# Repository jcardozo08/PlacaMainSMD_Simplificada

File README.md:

# PlacaMainSMD Simplificada

Mesma proposta da [PlacaMainSMD v1](https://github.com/jcardozo08/PlacaMainSMD_v1), mas com uma mistura de componentes **SMD e PTH** e com **módulos fáceis de encontrar** no mercado (GPS NEO-M8N, IMU GY-91, LoRa E32/E22) no lugar dos sensores soldados direto na placa. Assim ela fica mais barata, mais fácil de montar e de consertar em campo, e serve de alternativa robusta à v1.

## Destaques

- **ESP32-S3-WROOM-1**
- Conectores para GPS **u-blox NEO-M8N** e IMU **GY-91 / ICM-20948**
- Rádios LoRa **E22-900T22S** / **E32-915T20D** com conector SMA
- **4 canais de ignição** com MOSFETs SI2300, chave RBF, chave ON/OFF e buzzer
- Bateria de backup **ML414H** e porta USB-A
- **Gerbers** e arquivos de montagem **JLCPCB** incluídos
- Firmware: [FlightCode](https://github.com/jcardozo08/FlightCode) (`PLACA_MAIN_SMD`) / [FlightComputerRTOS](https://github.com/jcardozo08/FlightComputerRTOS)

| Topo | Base |
|:---:|:---:|
|  |  |

## Arquivos

- `PlacaMainSMD_Simplificada.kicad_sch`: esquemático ([ver em SVG](images/schematic.svg))
- `PlacaMainSMD_Simplificada.kicad_pcb`: layout da placa ([ver em SVG](images/layout.svg))
- `jlcpcb/`: Gerbers, furação, BOM e CPL para fabricação
- `PlacaMainSMD_Simplificada.step`: modelo 3D

**Ferramenta:** KiCad

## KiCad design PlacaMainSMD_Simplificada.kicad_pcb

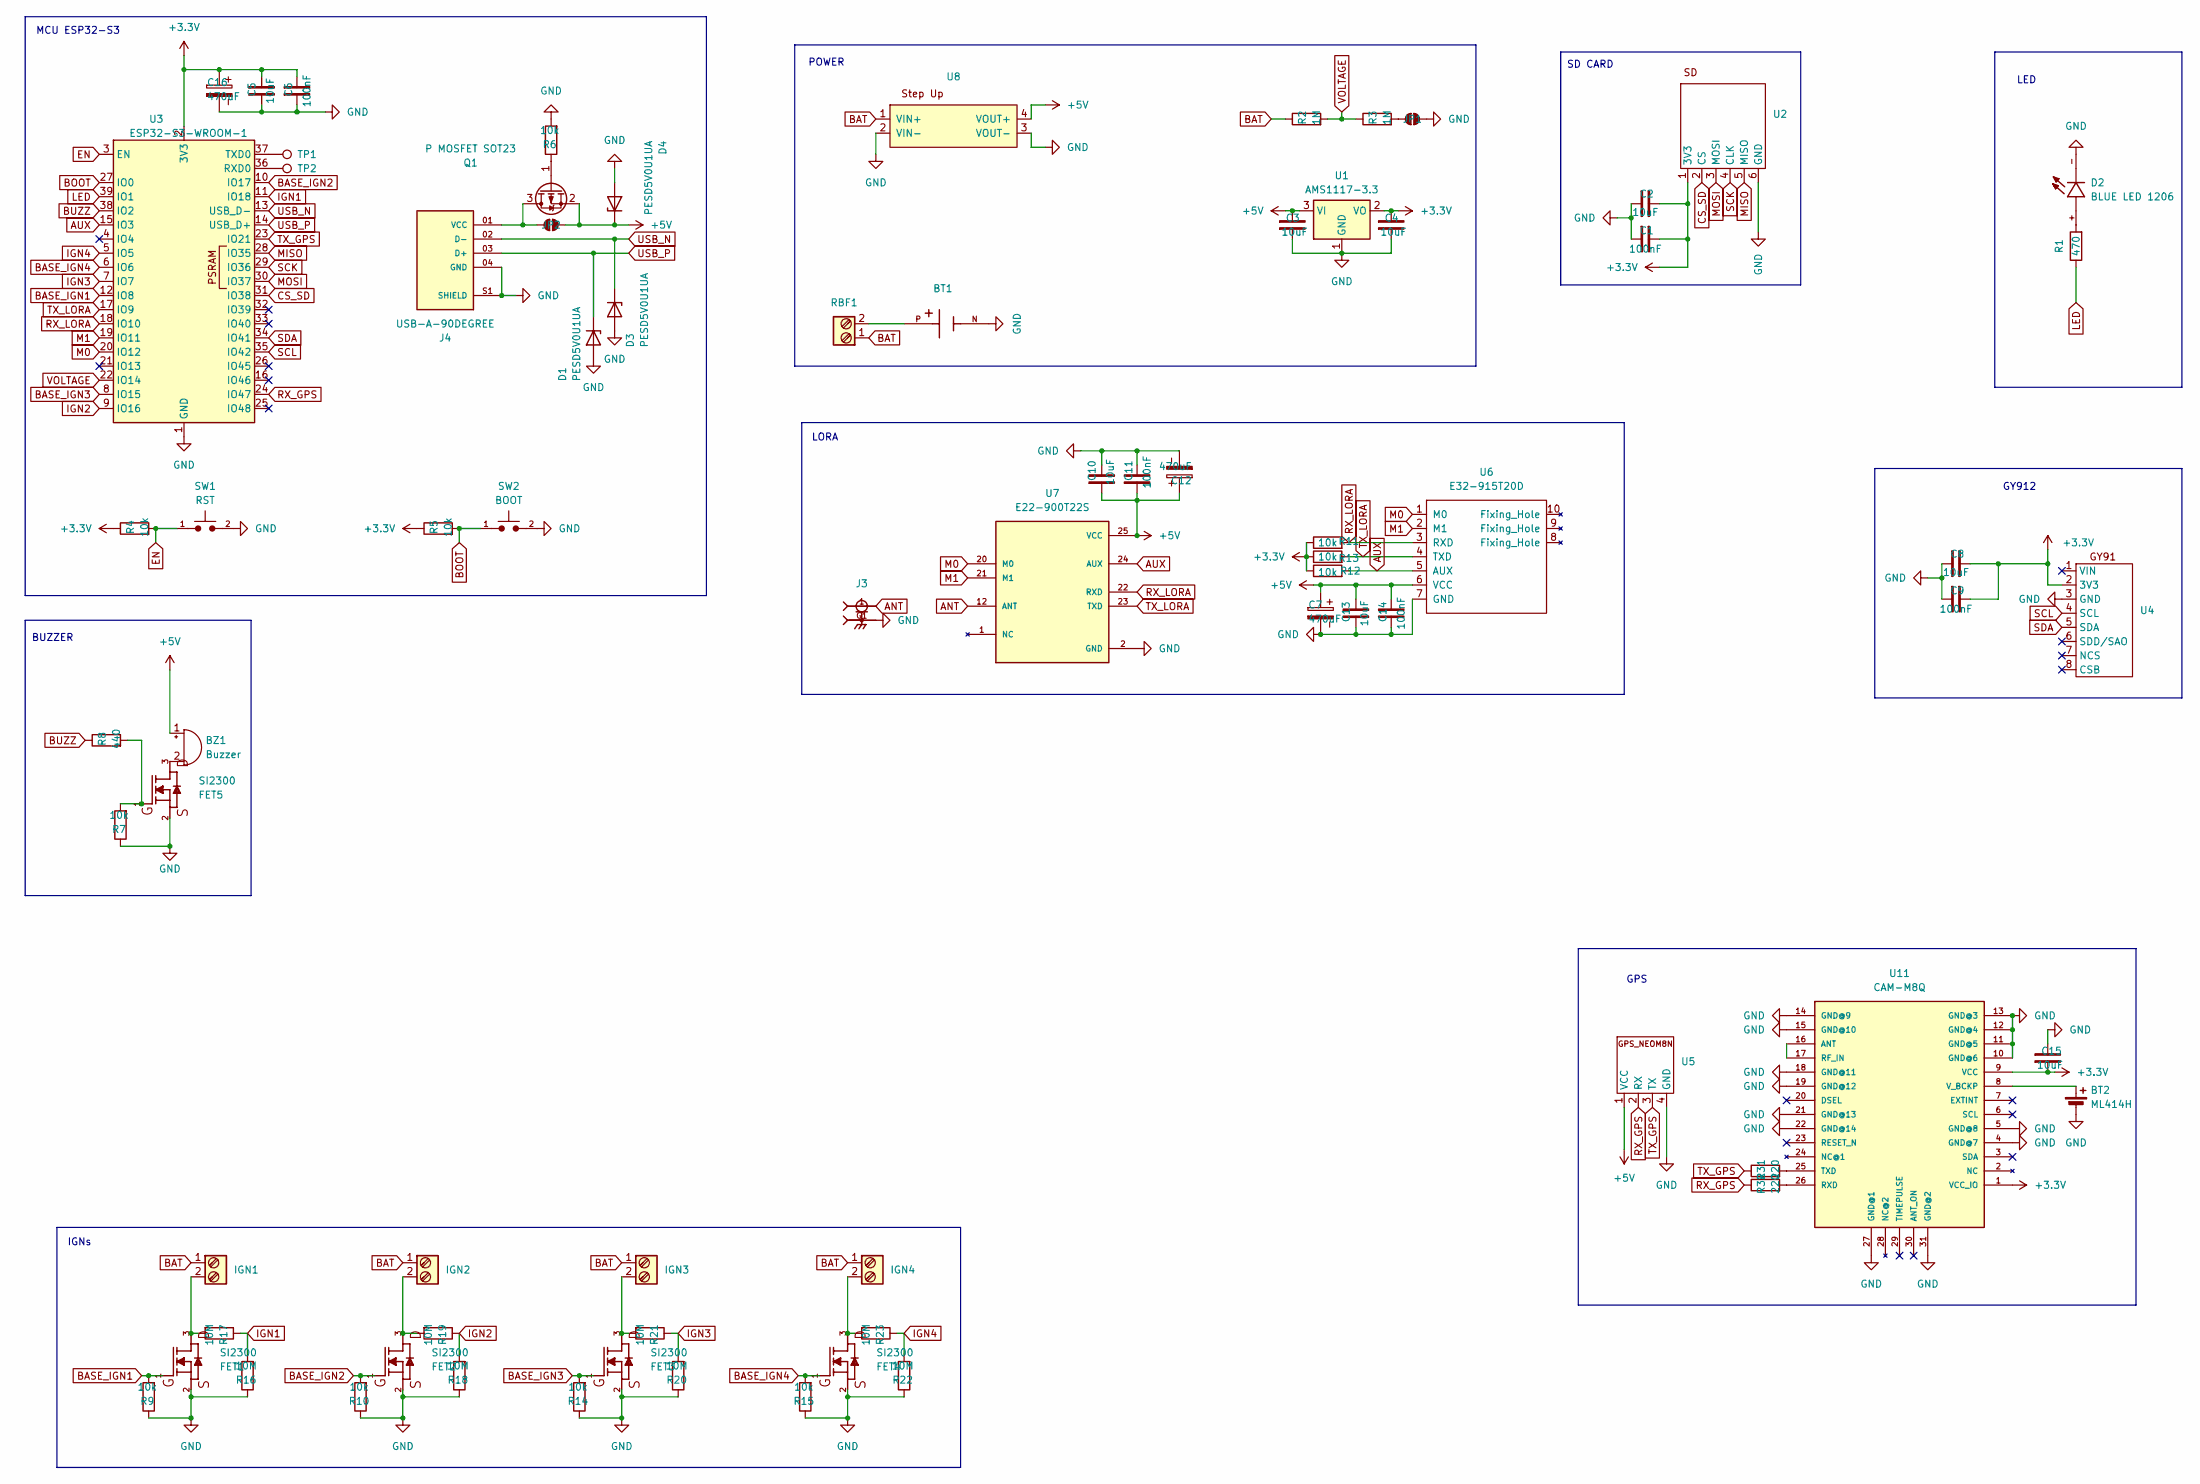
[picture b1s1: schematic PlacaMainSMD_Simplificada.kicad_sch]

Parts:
BT1: 18650_SMD
BT2: ML414H; ML414H_IV01E
BZ1: Buzzer
C1, C6, C9, C11, C14: 100nF; C_0805_2012Metric_Pad1.18x1.45mm_HandSolder
C2, C3, C4, C5, C8, C10, C13, C15: 10uF; C_0805_2012Metric_Pad1.18x1.45mm_HandSolder
C7, C12, C16: 470uF; CP_Radial_D5.0mm_P2.50mm
D1, D3, D4: PESD5V0U1UA; D_SOD-323_HandSoldering
D2: BLUE LED 1206; LED_SMD_1206; PARTREV 2002-04-11
FET1, FET2, FET3, FET4, FET5: SI2300; SOT23_SI2300
IGN1: IGN1; Borne 2 Vias
IGN2: IGN2; Borne 2 Vias
IGN3: IGN3; Borne 2 Vias
IGN4: IGN4; Borne 2 Vias
J3: ConectorSMA_EdgeMount; PARTREV 1
J4: USB-A-90DEGREE; PARTREV R
JP1, JP2: Jumper_2_NO
Q1: P MOSFET SOT23; SOT-23
R1: 470; R_0805_2012Metric_Pad1.20x1.40mm_HandSolder
R2, R3: 1M; R_0805_2012Metric_Pad1.20x1.40mm_HandSolder
R4, R5, R6, R7, R9, R10, R11, R12, R13, R14, R15: 10k; R_0805_2012Metric_Pad1.20x1.40mm_HandSolder
R8: 440; R_0805_2012Metric_Pad1.20x1.40mm_HandSolder
R16, R17, R18, R19, R20, R21, R22, R23: 10M; R_0805_2012Metric_Pad1.20x1.40mm_HandSolder
R31, R32: 220; R_0805_2012Metric_Pad1.20x1.40mm_HandSolder
RBF1: RBF1; Borne 2 Vias
SW1: RST; SW_PUSH_6mm
SW2: BOOT; SW_PUSH_6mm
TP1, TP2: TestPoint
U1: AMS1117-3.3; SOT-223-3_TabPin2
U2: MicroSD_Module_3.3V
U3: ESP32-S3-WROOM-1
U4: GY-91_Module
U5: GPS_NeoM8N
U6: E32-915T20D; E32-xxxT20D
U7: E22-900T22S; PARTREV 1.00
U8: Step Up
U11: CAM-M8Q; CAM-M8

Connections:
+3.3V: C1.2, C2.2, C4.2, C5.2, C6.2, C8.2, C9.2, C15.1, C16.1, R4.1, R5.1, R11.1, R12.1, R13.1, U1.2 (VO), U2.1 (3V3), U3.2 (3V3), U4.2 (3V3), U11.1 (VCC_IO), U11.9 (VCC)
+5V: BZ1.1 (+), C3.2, C7.1, C10.1, C11.1, C12.1, C13.2, C14.2, D4.1 (K), JP2.2 (B), Q1.2 (S), U1.3 (VI), U5.1 (VCC), U6.6 (VCC), U7.25 (VCC), U8.4 (VOUT+)
ANT: J3.1, U7.12 (ANT)
AUX: R13.2, U3.15 (IO3), U6.5 (AUX), U7.24 (AUX)
BASE_IGN1: FET1.1, R9.2, U3.12 (IO8)
BASE_IGN2: FET2.1, R10.2, U3.10 (IO17)
BASE_IGN3: FET3.1, R14.2, U3.8 (IO15)
BASE_IGN4: FET4.1, R15.2, U3.6 (IO6)
BAT: IGN1.1, IGN2.1, IGN3.1, IGN4.1, R2.1, RBF1.1, U8.1 (VIN+)
BOOT: R5.2, SW2.1, U3.27 (IO0)
BUZZ: R8.1, U3.38 (IO2)
CS_SD: U2.2 (CS), U3.31 (IO38)
EN: R4.2, SW1.1, U3.3 (EN)
GND: BT1.N, BT2.-, C1.1, C2.1, C3.1, C4.1, C5.1, C6.1, C7.2, C8.1, C9.1, C10.2, C11.2, C12.2, C13.1, C14.1, C15.2, C16.2, D1.2 (A), D2.-, D3.2 (A), D4.2 (A), FET1.2, FET2.2, FET3.2, FET4.2, FET5.2, J3.G1, J3.G2, J3.G3, J3.G4, J4.04 (GND), J4.S1 (SHIELD), J4.S2 (SHIELD), JP1.2 (B), R6.2, R7.1, R9.1, R10.1, R14.1, R15.1, R16.1, R18.1, R20.1, R22.1, SW1.2, SW2.2, U1.1 (GND), U2.6 (GND), U3.1 (GND), U3.40 (GND), U3.41 (GND), U4.3 (GND), U5.4 (GND), U6.7 (GND), U7.2 (GND), U7.8 (GND), U7.11 (GND), U7.13 (GND), U7.14 (GND), U7.15 (GND), U7.16 (GND), U7.19 (GND), U7.26 (GND), U8.2 (VIN-), U8.3 (VOUT-), U11.4 (GND@7), U11.5 (GND@8), U11.10 (GND@6), U11.11 (GND@5), U11.12 (GND@4), U11.13 (GND@3), U11.14 (GND@9), U11.15 (GND@10), U11.18 (GND@11), U11.19 (GND@12), U11.21 (GND@13), U11.22 (GND@14), U11.27 (GND@1), U11.31 (GND@2)
IGN1: R16.2, R17.1, U3.11 (IO18)
IGN2: R18.2, R19.1, U3.9 (IO16)
IGN3: R20.2, R21.1, U3.7 (IO7)
IGN4: R22.2, R23.1, U3.5 (IO5)
LED: R1.1, U3.39 (IO1)
M0: U3.20 (IO12), U6.1 (M0), U7.20 (M0)
M1: U3.19 (IO11), U6.2 (M1), U7.21 (M1)
MISO: U2.5 (MISO), U3.28 (IO35)
MOSI: U2.3 (MOSI), U3.30 (IO37)
unnamed: BT1.P, RBF1.2
unnamed: BZ1.2 (-), FET5.3
unnamed: D2.+, R1.2
unnamed: FET1.3, IGN1.2, R17.2
unnamed: FET2.3, IGN2.2, R19.2
unnamed: FET3.3, IGN3.2, R21.2
unnamed: FET4.3, IGN4.2, R23.2
unnamed: FET5.1, R7.2, R8.2
unnamed: J4.01 (VCC), JP2.1 (A), Q1.3 (D)
unnamed: JP1.1 (A), R3.2
unnamed: Q1.1 (G), R6.1
unnamed: TP2.1, U3.36 (RXD0)
unnamed: TP1.1, U3.37 (TXD0)
unnamed: U11.16 (ANT), U11.17 (RF_IN)
unnamed: R32.2, U11.26 (RXD)
unnamed: R31.2, U11.25 (TXD)
unnamed: BT2.+, U11.8 (V_BCKP)
RX_GPS: R32.1, U3.24 (IO47), U5.2 (RX)
RX_LORA: R11.2, U3.18 (IO10), U6.3 (RXD), U7.22 (RXD)
SCK: U2.4 (CLK), U3.29 (IO36)
SCL: U3.35 (IO42), U4.4 (SCL)
SDA: U3.34 (IO41), U4.5 (SDA)
TX_GPS: R31.1, U3.23 (IO21), U5.3 (TX)
TX_LORA: R12.2, U3.17 (IO9), U6.4 (TXD), U7.23 (TXD)
USB_N: D3.1 (K), J4.02 (D-), U3.13 (USB_D-)
USB_P: D1.1 (K), J4.03 (D+), U3.14 (USB_D+)
VOLTAGE: R2.2, R3.1, U3.22 (IO14)

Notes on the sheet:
MCU ESP32-S3
LORA
GPS
GY912
LED
SD CARD
BUZZER
IGNs
POWER

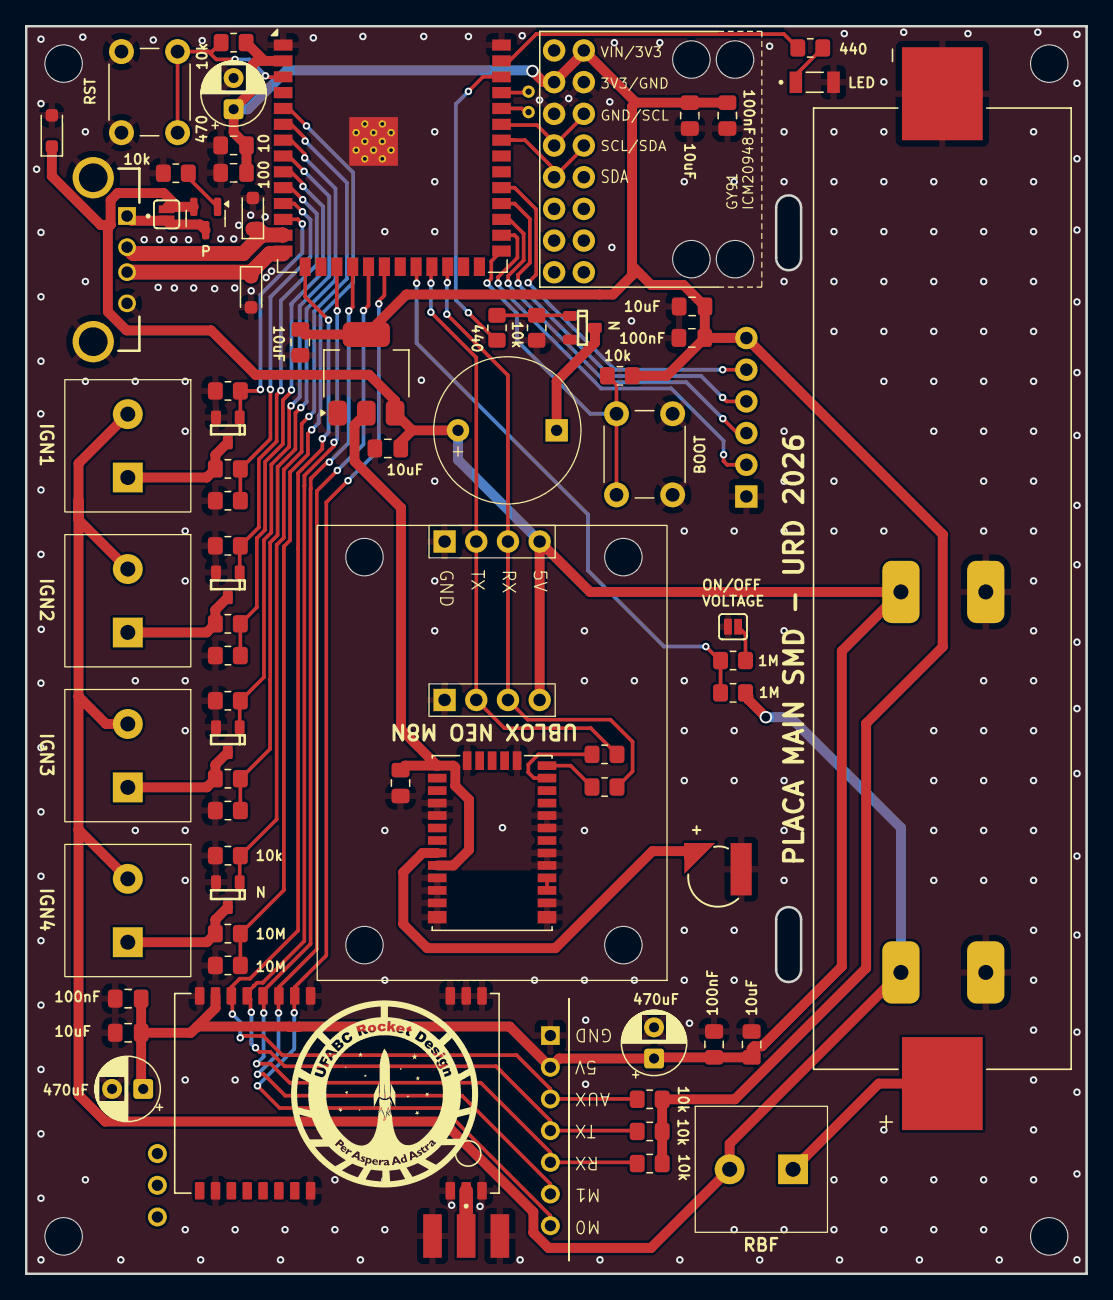
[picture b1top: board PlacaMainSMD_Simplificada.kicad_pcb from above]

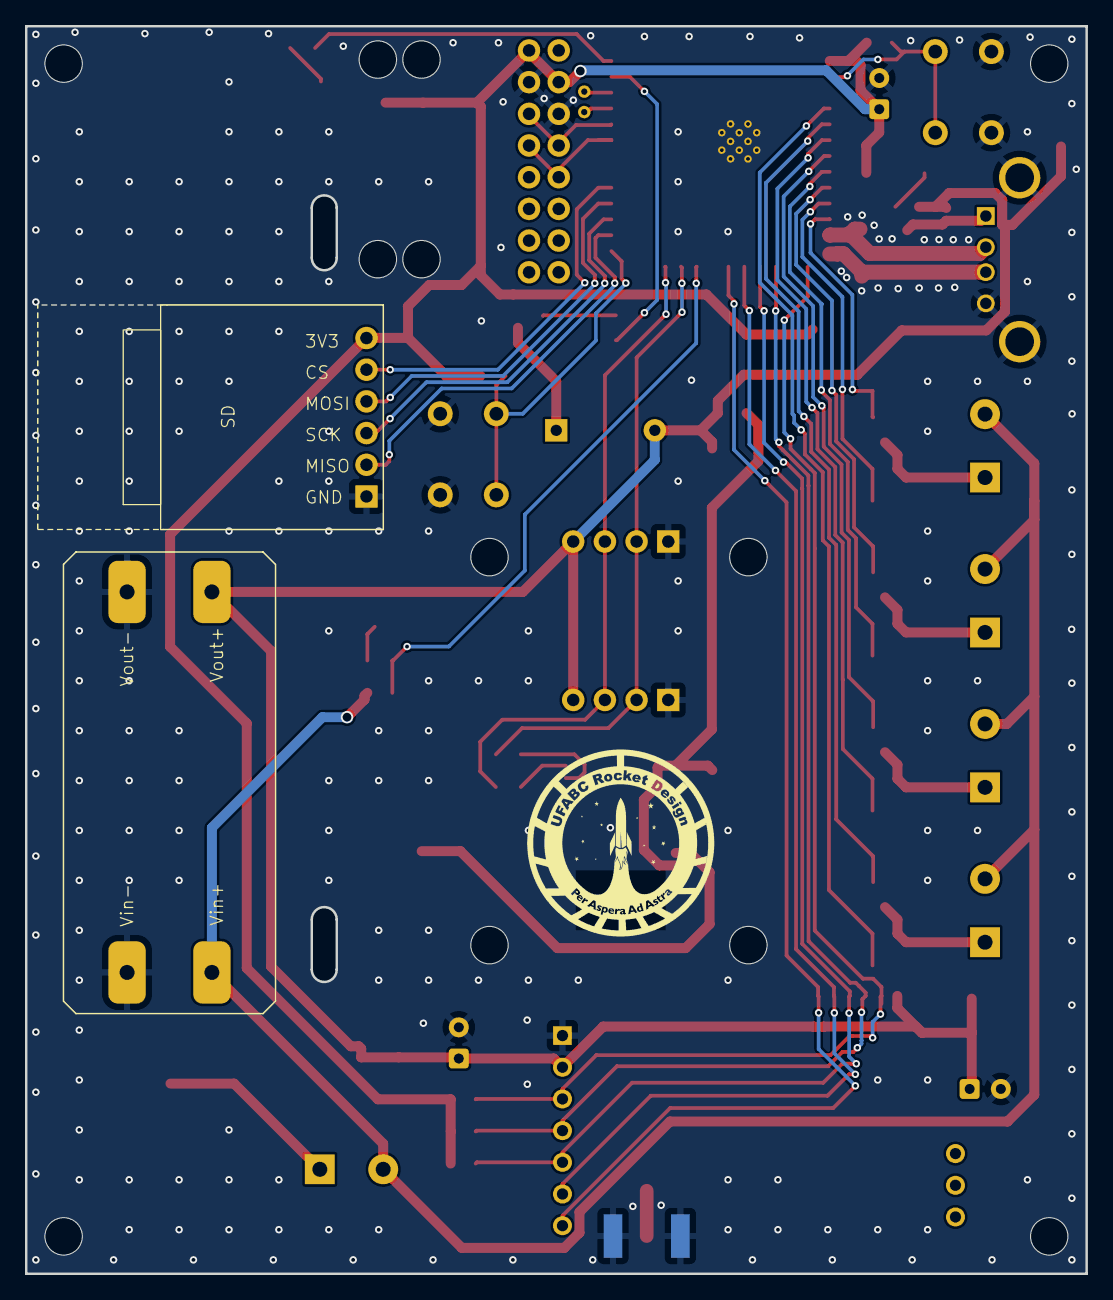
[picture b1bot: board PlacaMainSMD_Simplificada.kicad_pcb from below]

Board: 2 copper layers, 85.0 x 100.0 mm, 82 parts (3 on the bottom side), 50 nets.

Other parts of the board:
G1, G1#2: LOGO; LogoRocket
NPTH7, NPTH8, NPTH9, NPTH10: (no value)
